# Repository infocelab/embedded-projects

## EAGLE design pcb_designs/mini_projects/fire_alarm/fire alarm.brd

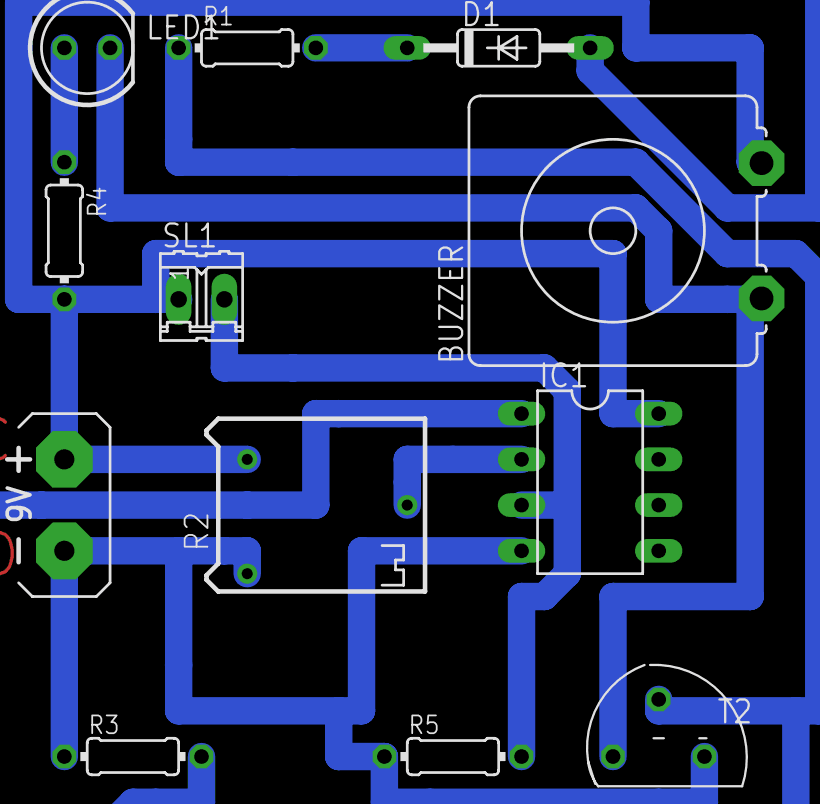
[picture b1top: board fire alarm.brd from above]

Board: 2 copper layers, 12 parts (0 on the bottom side), 9 nets.

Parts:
BUZZER: B/C11L
D1: 1N4007S; DO35-10
G1: AB9V
IC1: LM358; DIL-08
LED1: 5mm; LED5MM
R1: 10k; 0204/7
R2: 500K; RTRIM64P
R3: 10K; 0204/7
R4: 220E; 0204/7
R5: 100K; 0204/7
SL1: NTC104; 02P
T2: BC547; TO92

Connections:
unnamed: D1.A, IC1.1
unnamed: D1.C, R1.2
unnamed: R1.1, R3.2, T2.2
unnamed: G1.-, IC1.4, R2.1, R3.1, R5.1, T2.1
unnamed: BUZZER.1, LED1.K, T2.3
unnamed: LED1.A, R4.1
unnamed: IC1.2, R2.2
unnamed: IC1.3, R5.2, SL1.2
unnamed: BUZZER.2, G1.+, IC1.8, R2.3, R4.2, SL1.1

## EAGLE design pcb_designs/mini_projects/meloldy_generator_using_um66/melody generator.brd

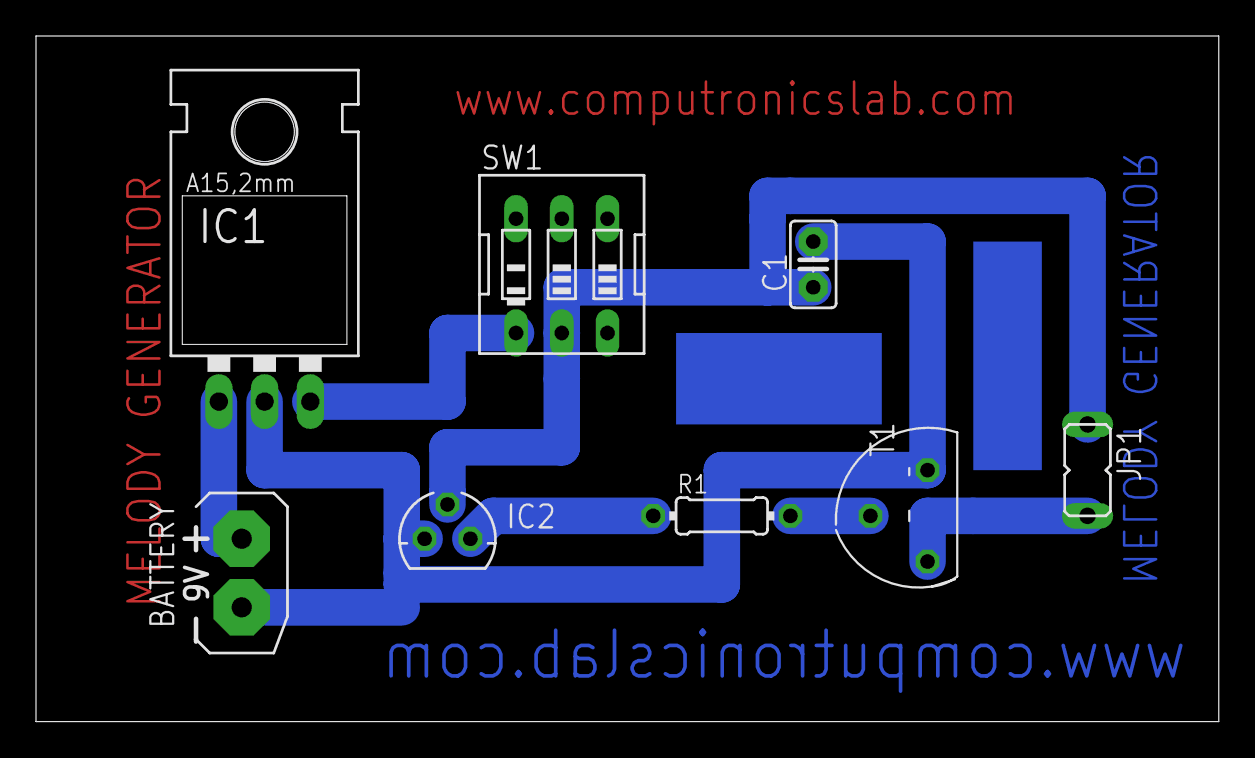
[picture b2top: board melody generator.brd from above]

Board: 2 copper layers, 65.7 x 38.1 mm, 8 parts (0 on the bottom side), 7 nets.

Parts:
BATTERY: A9V; AB9V
C1: 0.1uf; C2.5-2
IC1: 7805; 78XXL
IC2: UM66; 79LXX
JP1: spekar; JP1
R1: 4.7k; 0204/7
SW1: on/off switch; EDG-03
T1: BC547; TO92

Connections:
unnamed: IC2.OUT, R1.1
unnamed: R1.2, T1.2
unnamed: BATTERY.+, IC1.IN
unnamed: BATTERY.-, C1.2, IC1.GND, IC2.GND, T1.1
unnamed: IC1.OUT, SW1.1
unnamed: C1.1, IC2.IN, JP1.1, SW1.2
unnamed: JP1.2, T1.3

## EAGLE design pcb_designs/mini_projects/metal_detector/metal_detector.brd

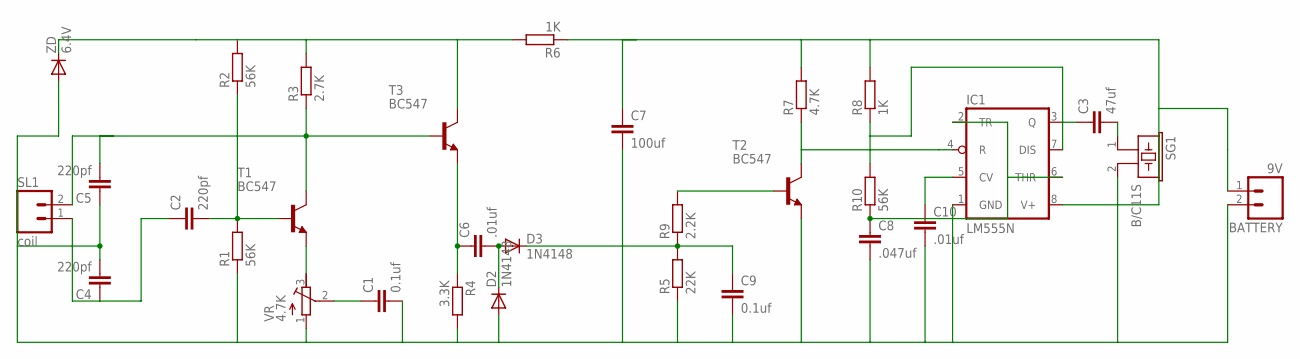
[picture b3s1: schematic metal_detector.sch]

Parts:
BATTERY: 9V; 02P
C1, C9: 0.1uf; C2.5-4
C2, C4, C5: 220pf; C2.5-4
C3: 47uf; C2.5-4
C6, C10: .01uf; C2.5-4
C7: 100uf; C2.5-4
C8: .047uf; C2.5-4
D2, D3: 1N4148; DO41-10
IC1: LM555N; DIL08
R1, R2, R10: 56K; 0204/7
R3: 2.7K; 0204/7
R4: 3.3K; 0204/7
R5: 22K; 0204/7
R6, R8: 1K; 0204/7
R7: 4.7K; 0204/7
R9: 2.2K; 0204/7
SG1: B/C11S
SL1: coil; 02P
T1, T2, T3: BC547; TO92
VR: 4.7K; RTRIM64P
ZD: 6.4V; DO41-10

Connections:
unnamed: C2.2, R1.2, R2.1, T1.2 (B)
unnamed: C5.2, R3.1, SL1.2, T1.3 (C), T3.2 (B)
unnamed: BATTERY.1, C7.1, IC1.8 (V+), R6.1, R7.2, R8.2
unnamed: C2.1, C4.1, SL1.1
unnamed: BATTERY.2, C1.2, C4.2, C5.1, C7.2, C8.2, C9.2, C10.2, D2.A, IC1.1 (GND), R1.1, R4.2, R5.1, SG1.2, T2.1 (E), VR.1 (E), ZD.A
unnamed: IC1.4 (R), R7.1, T2.3 (C)
unnamed: IC1.7 (DIS), R8.1, R10.2
unnamed: C8.1, IC1.2 (TR), IC1.6 (THR), R10.1
unnamed: T1.1 (E), VR.3 (A)
unnamed: C1.1, VR.2 (S)
unnamed: C6.1, R4.1, T3.1 (E)
unnamed: C6.2, D2.C, D3.A
unnamed: C3.2, SG1.1
unnamed: C9.1, D3.C, R5.2, R9.1
unnamed: R9.2, T2.2 (B)
unnamed: C10.1, IC1.5 (CV)
unnamed: R2.2, R3.2, R6.2, T3.3 (C), ZD.C
unnamed: C3.1, IC1.3 (Q)

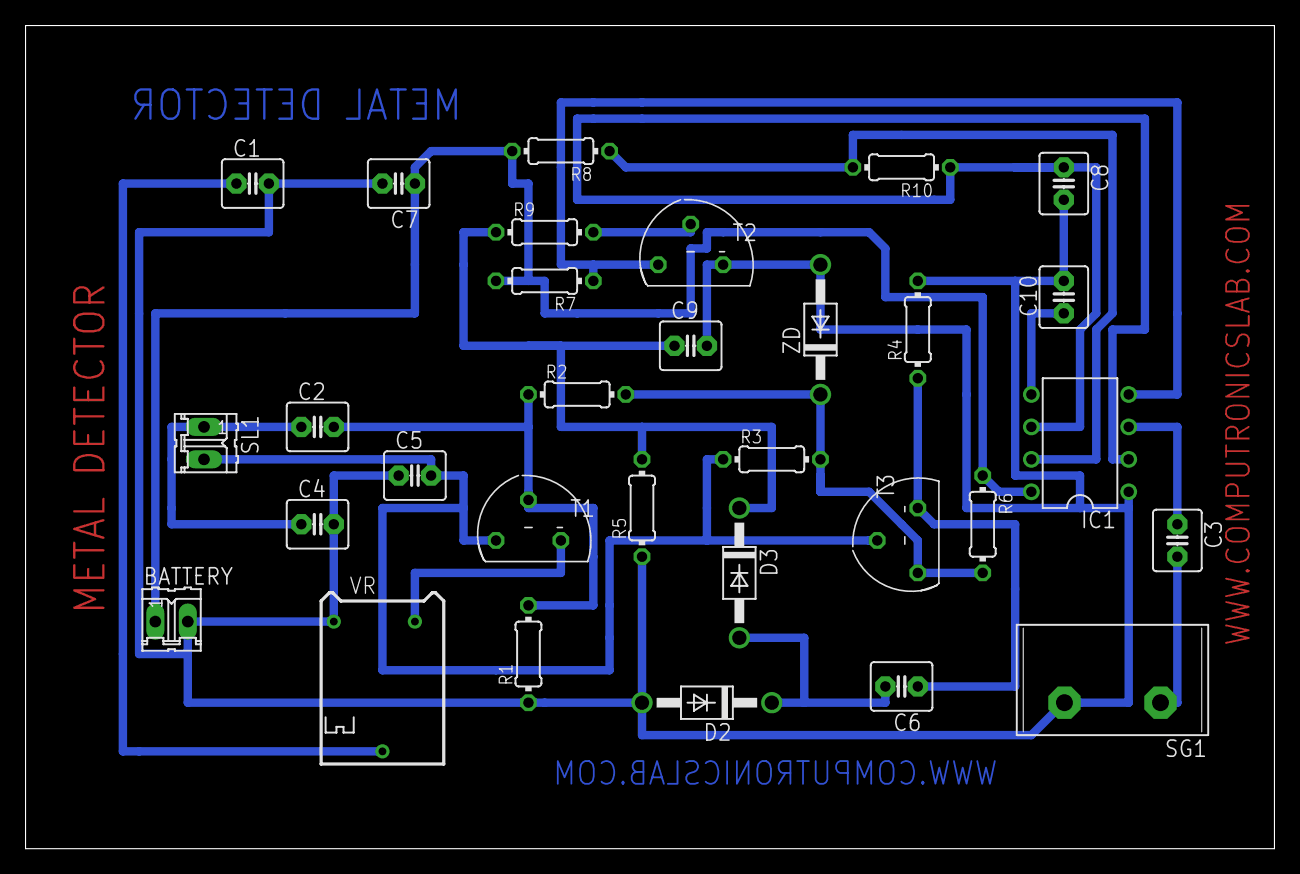
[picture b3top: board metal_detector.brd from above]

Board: 2 copper layers, 97.8 x 64.4 mm, 31 parts (0 on the bottom side), 18 nets.

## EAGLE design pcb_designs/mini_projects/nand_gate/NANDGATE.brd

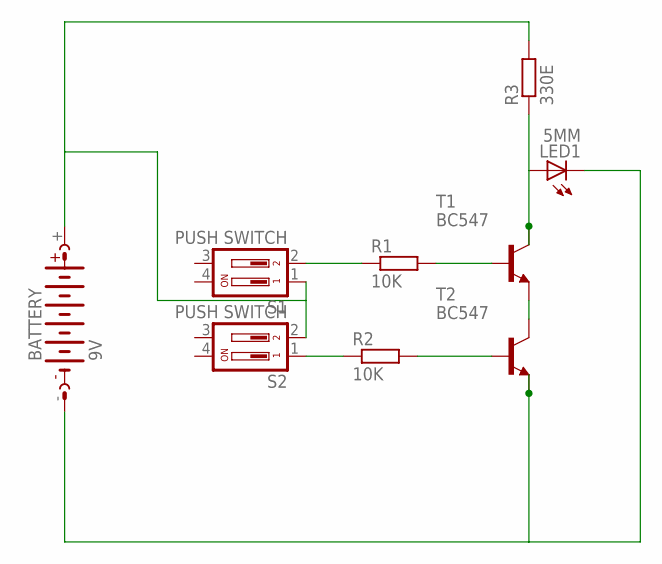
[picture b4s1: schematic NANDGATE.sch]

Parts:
BATTERY: 9V; AB9V
LED1: 5MM; LED5MM
R1, R2: 10K; 0204/7
R3: 330E; 0204/7
S1, S2: PUSH SWITCH; DS-02
T1, T2: BC547; TO92

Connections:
unnamed: R1.2, T1.2 (B)
unnamed: R2.2, T2.2 (B)
unnamed: T1.1 (E), T2.3 (C)
unnamed: LED1.A, R3.1, T1.3 (C)
unnamed: BATTERY.+, R3.2, S1.1, S2.2
unnamed: BATTERY.-, LED1.K (C), T2.1 (E)
unnamed: R2.1, S2.1
unnamed: R1.1, S1.2

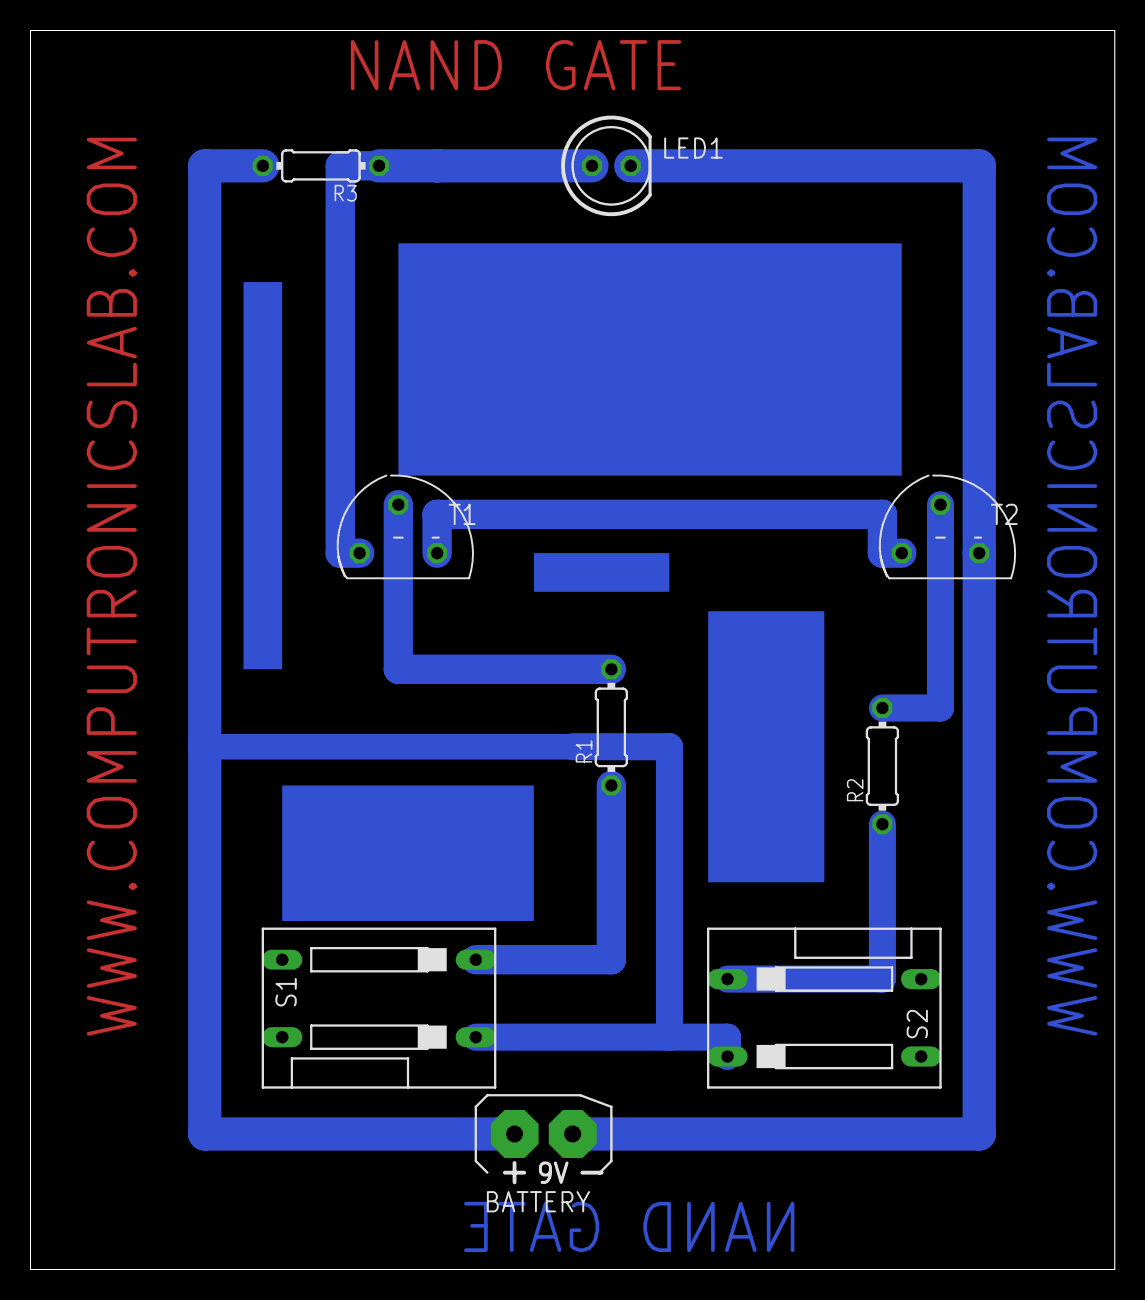
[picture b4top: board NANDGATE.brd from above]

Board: 2 copper layers, 71.1 x 81.3 mm, 9 parts (0 on the bottom side), 8 nets.

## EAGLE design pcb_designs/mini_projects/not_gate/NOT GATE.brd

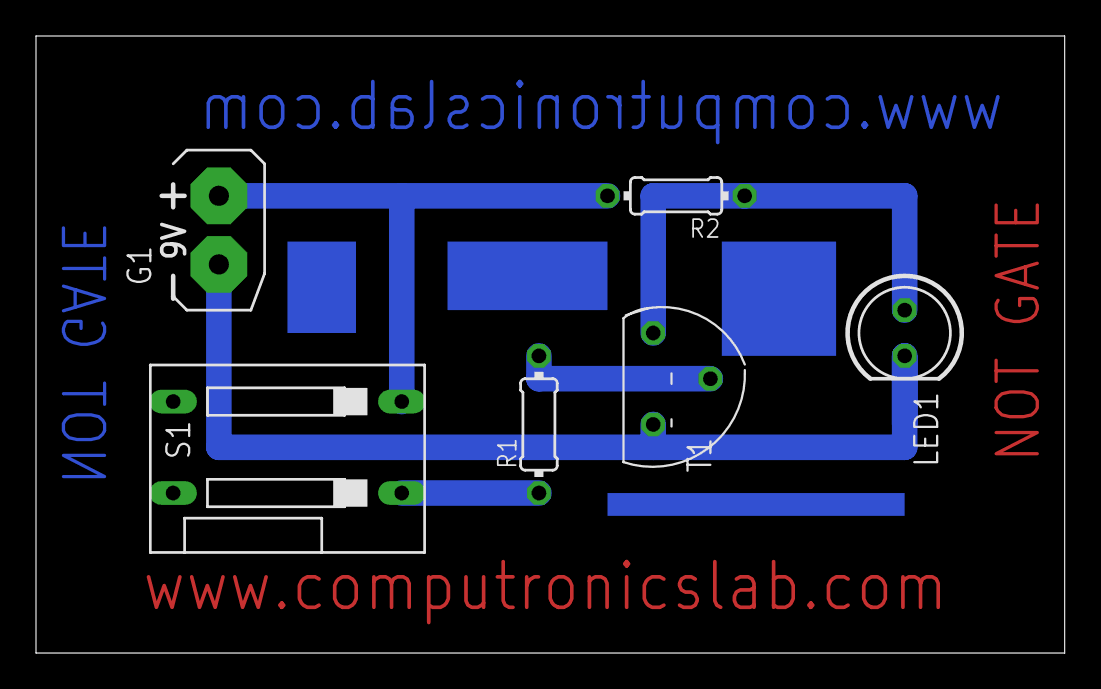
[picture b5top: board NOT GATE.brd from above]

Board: 2 copper layers, 57.2 x 34.3 mm, 6 parts (0 on the bottom side), 5 nets.

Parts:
G1: AB9V
LED1: LED5MM
R1, R2: 0204/7
S1: DS-02
T1: BC547; TO92

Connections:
unnamed: R1.2, T1.2
unnamed: LED1.A, R2.1, T1.3
unnamed: R1.1, S1.1
unnamed: G1.+, R2.2, S1.2
unnamed: G1.-, LED1.K, T1.1

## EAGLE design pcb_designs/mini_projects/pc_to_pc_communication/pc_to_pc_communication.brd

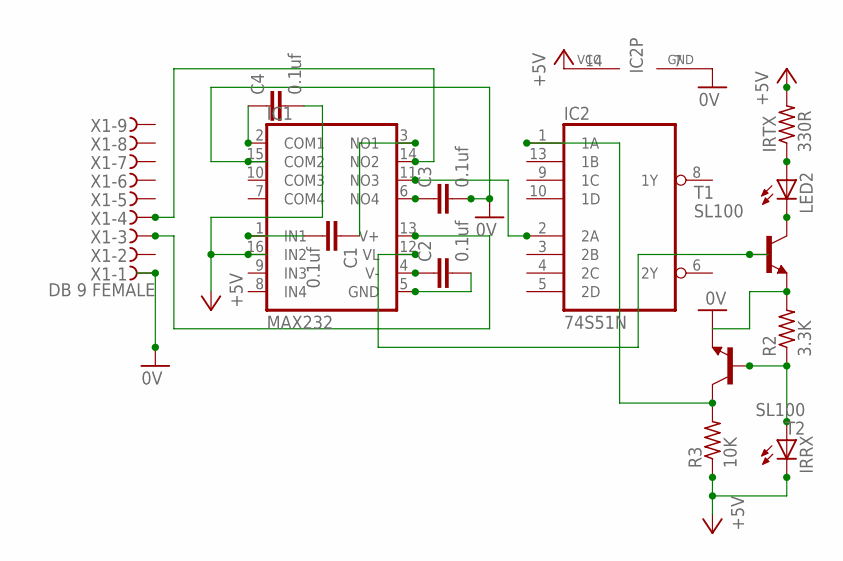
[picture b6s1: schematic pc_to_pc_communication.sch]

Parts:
C1, C2, C3, C4: 0.1uf; C2.5-3
IC1: MAX232; DIL16
IC2: 74S51N; DIL14
IRRX: LED3MM
IRTX: 330R; 0204/7
LED2: LED3MM
R2: 3.3K; 0204/7
R3: 10K; 0204/7
T1, T2: SL100; TO5
X1: DB 9 FEMALE; H2M09ST

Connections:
0V: C3.2, IC1.15 (COM2), IC2.7 (GND), R2.2, T1.1 (E), T2.1 (E), X1.1
+5V: C4.2, IC1.16 (IN2), IC2.14 (VCC), IRRX.K (C), IRTX.2, R3.1
unnamed: C1.2, IC1.1 (IN1)
unnamed: C1.1, IC1.3 (NO1)
unnamed: C2.1, IC1.4 (V-)
unnamed: C2.2, IC1.5 (GND)
unnamed: C3.1, IC1.6 (NO4)
unnamed: LED2.K (C), T1.3 (C)
unnamed: C4.1, IC1.2 (COM1)
unnamed: IRTX.1, LED2.A
unnamed: IC1.13 (V+), X1.3
unnamed: IC1.14 (NO2), X1.4
unnamed: IC1.11 (NO3), IC2.2 (2A)
unnamed: IC1.12 (VL), T1.2 (B)
unnamed: IRRX.A, R2.1, T2.2 (B)
unnamed: IC2.1 (1A), R3.2, T2.3 (C)

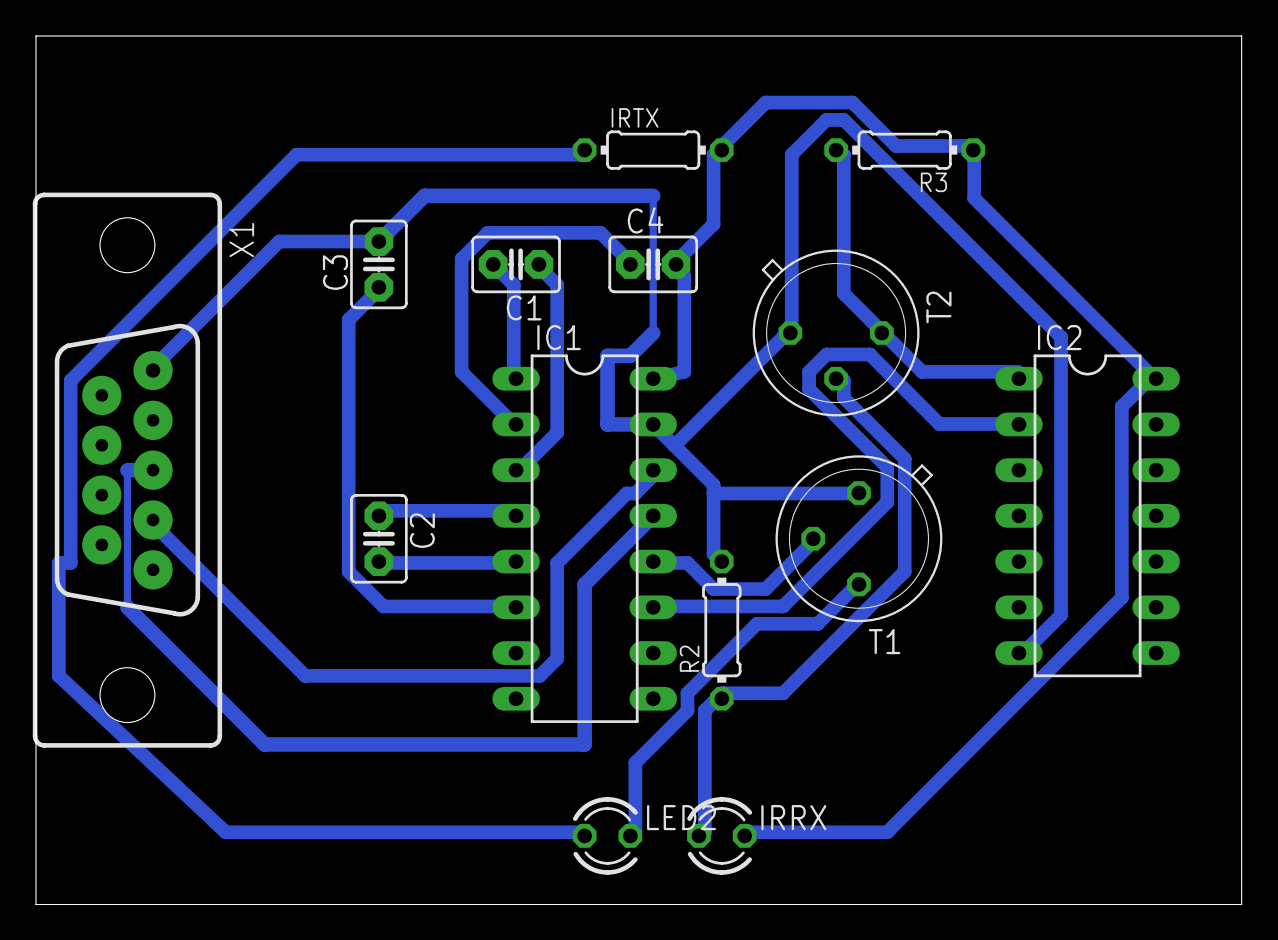
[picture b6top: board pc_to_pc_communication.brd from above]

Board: 2 copper layers, 67.0 x 48.2 mm, 14 parts (0 on the bottom side), 16 nets.

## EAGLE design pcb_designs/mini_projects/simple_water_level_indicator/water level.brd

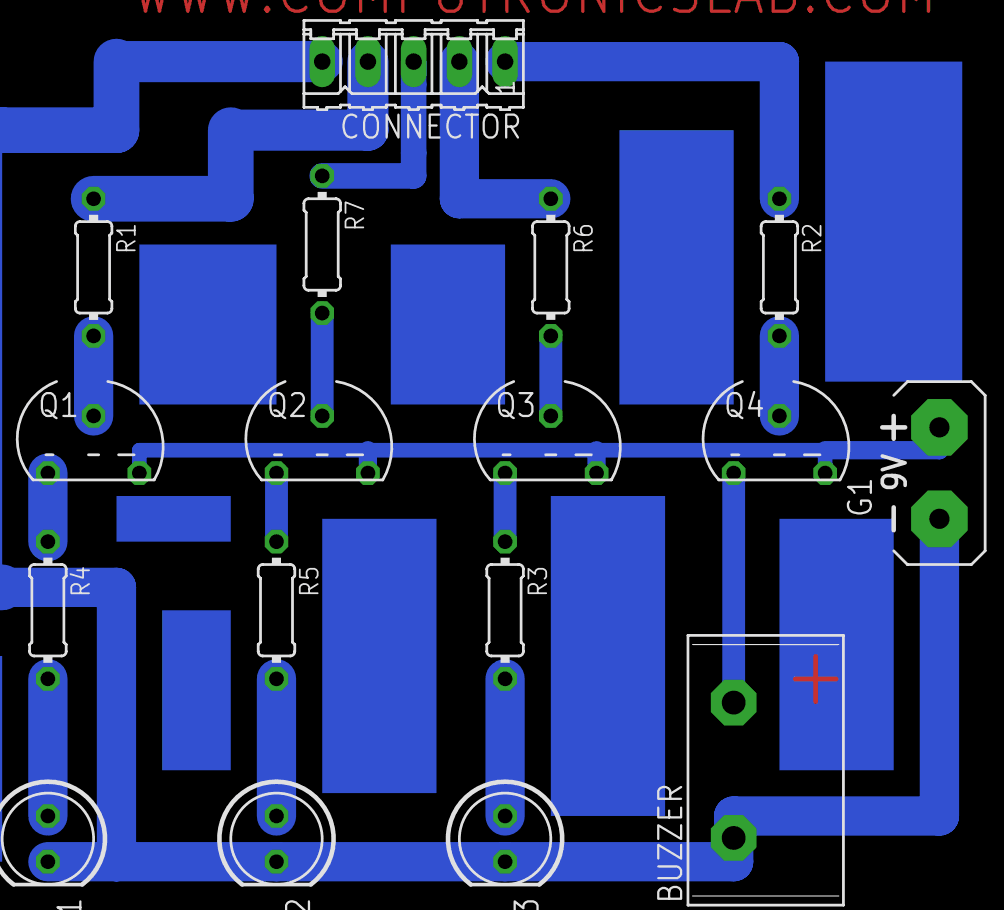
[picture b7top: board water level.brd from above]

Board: 2 copper layers, 17 parts (0 on the bottom side), 17 nets.

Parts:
BUZZER: B/C11S
CONNECTOR: 05P
G1: AB9V
LED1, LED2, LED3: 5mm; LED5MM
Q1, Q2, Q3, Q4: BC557; TO92
R1, R2, R3, R4, R5, R6, R7: 470E; 0204/7

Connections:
unnamed: Q1.3, R4.1
unnamed: Q2.3, R5.1
unnamed: Q3.3, R3.1
unnamed: Q1.2, R1.2
unnamed: Q2.2, R7.2
unnamed: Q3.2, R6.2
unnamed: Q4.2, R2.2
unnamed: BUZZER.2, Q4.3
unnamed: LED1.A, R4.2
unnamed: LED3.A, R3.2
unnamed: G1.+, Q1.1, Q2.1, Q3.1, Q4.1
unnamed: BUZZER.1, CONNECTOR.5, G1.-, LED1.K, LED2.K, LED3.K
unnamed: CONNECTOR.2, R6.1
unnamed: CONNECTOR.3, R7.1
unnamed: CONNECTOR.4, R1.1
unnamed: CONNECTOR.1, R2.1
unnamed: LED2.A, R5.2

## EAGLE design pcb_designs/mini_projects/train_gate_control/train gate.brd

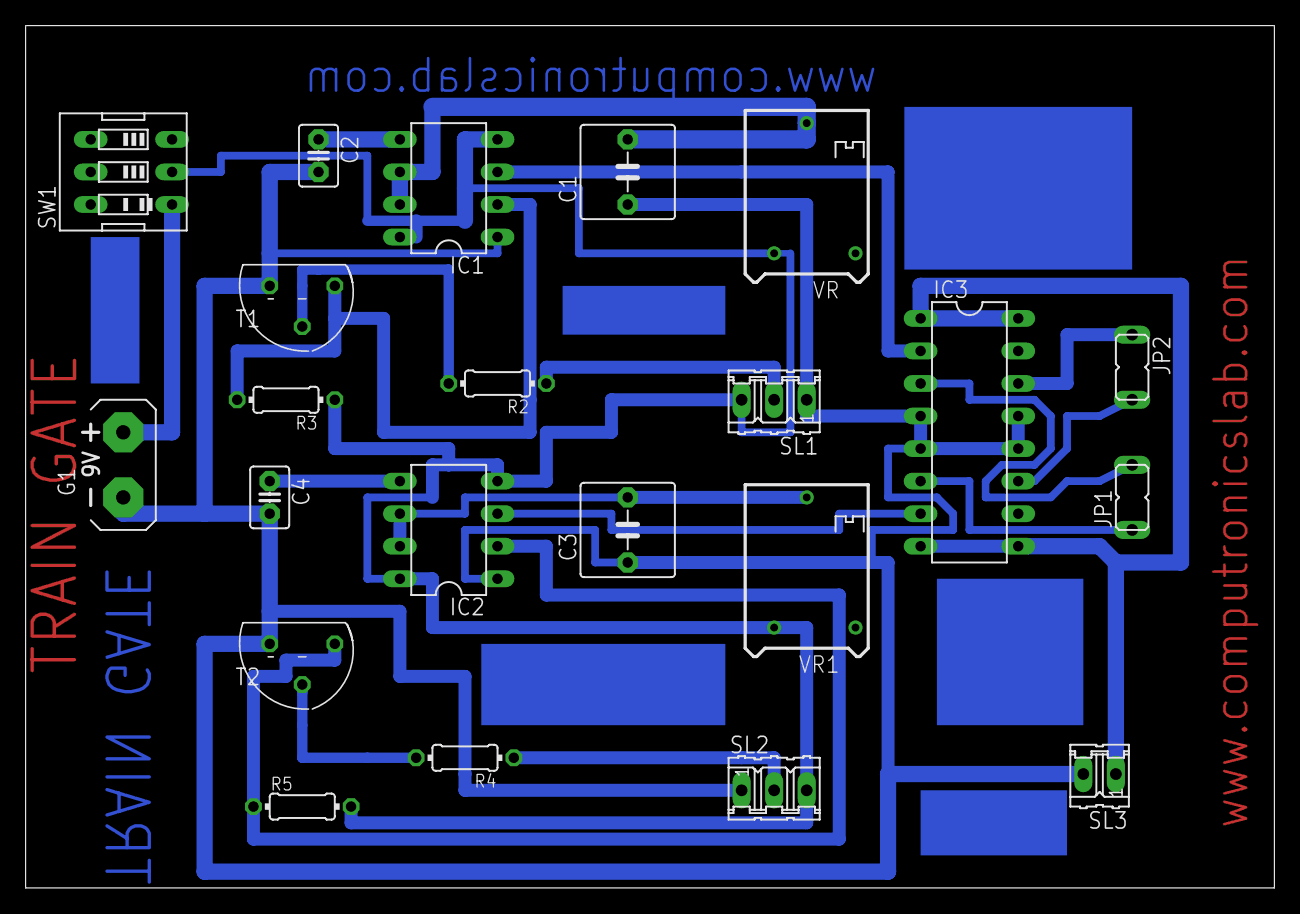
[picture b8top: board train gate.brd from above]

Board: 2 copper layers, 97.5 x 67.3 mm, 22 parts (0 on the bottom side), 20 nets.

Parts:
C1, C3: 100uf; C5B7.2
C2, C4: 0.1uf; C2.5-3
G1: AB9V
IC1, IC2: NE555; DIL-08
IC3: L293D; DIL16
JP1: motor1; JP1
JP2: motor2; JP1
R2, R4: 220E; 0204/7
R3, R5: 10K; 0204/7
SL1, SL2: ir module; 03P
SL3: supply; 02P
SW1: on/off switch; EDG-03
T1, T2: BC547; TO92
VR, VR1: 100k; RTRIM64P

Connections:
unnamed: C1.2, IC1.6, IC1.7, VR.2
unnamed: C3.2, IC2.6, IC2.7, VR1.2
unnamed: R2.1, SL1.2
unnamed: R4.1, SL2.2
unnamed: C2.1, IC1.5
unnamed: R4.2, T2.2
unnamed: G1.+, SW1.1
unnamed: IC1.2, R3.2, T1.3
unnamed: C4.1, IC2.5
unnamed: IC2.2, R5.1, T2.3
unnamed: C1.1, C2.2, C3.1, C4.2, G1.-, IC1.1, IC2.1, IC3.4, IC3.5, IC3.12, IC3.13, SL1.1, SL2.1, SL3.2, T1.1, T2.1
unnamed: IC3.1, IC3.8, IC3.9, IC3.16, SL3.1
unnamed: IC1.4, IC1.8, IC2.4, IC2.8, R3.1, R5.2, SL1.3, SL2.3, SW1.2, VR.3, VR1.3
unnamed: R2.2, T1.2
unnamed: IC3.3, JP1.2
unnamed: IC3.6, JP1.1
unnamed: IC3.14, JP2.1
unnamed: IC3.11, JP2.2
unnamed: IC1.3, IC3.2
unnamed: IC2.3, IC3.7
